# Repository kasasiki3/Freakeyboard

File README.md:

# Freakeyboard
You enter keys into your PC by swiping and touching just like on a smartphone keyboard.

This keyboarad has 23tuch senser and Raspberry Pi pico .

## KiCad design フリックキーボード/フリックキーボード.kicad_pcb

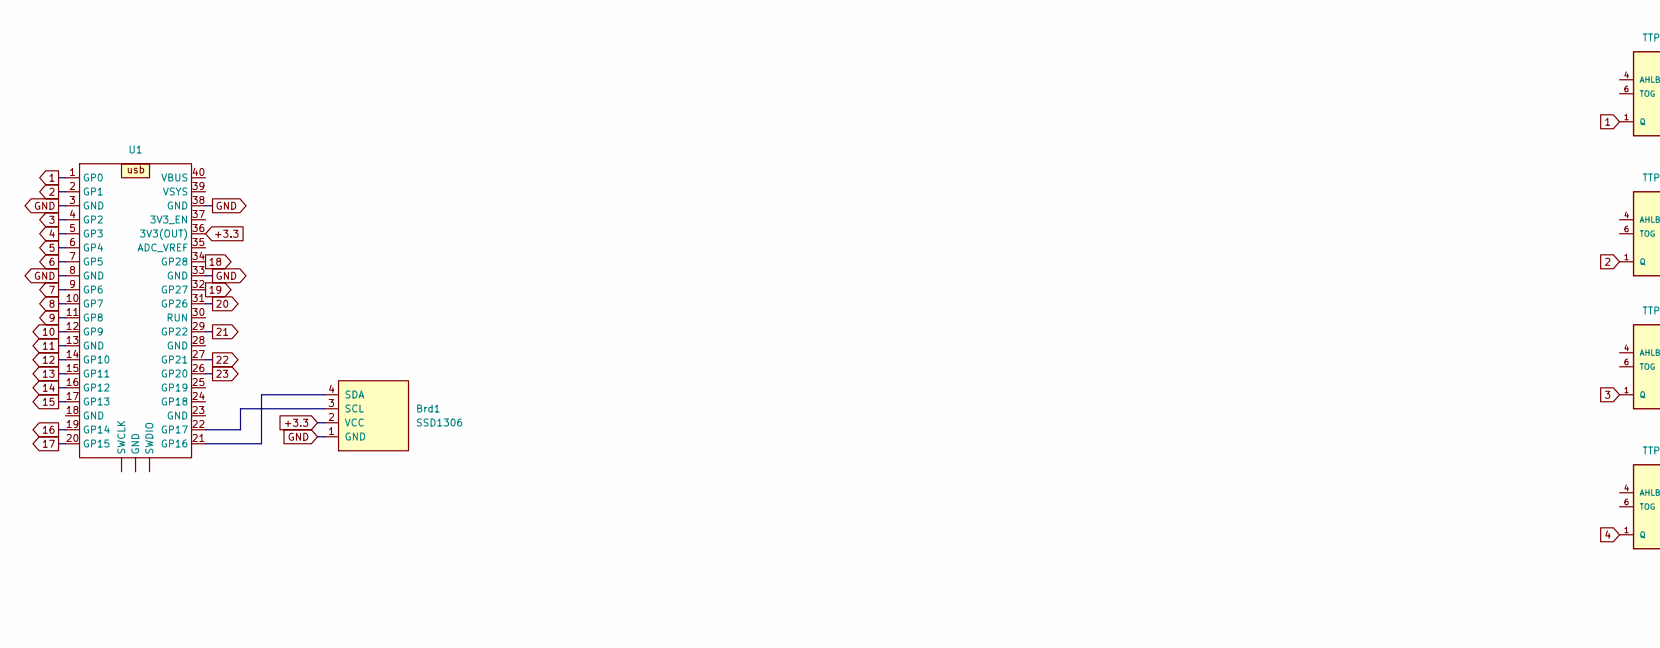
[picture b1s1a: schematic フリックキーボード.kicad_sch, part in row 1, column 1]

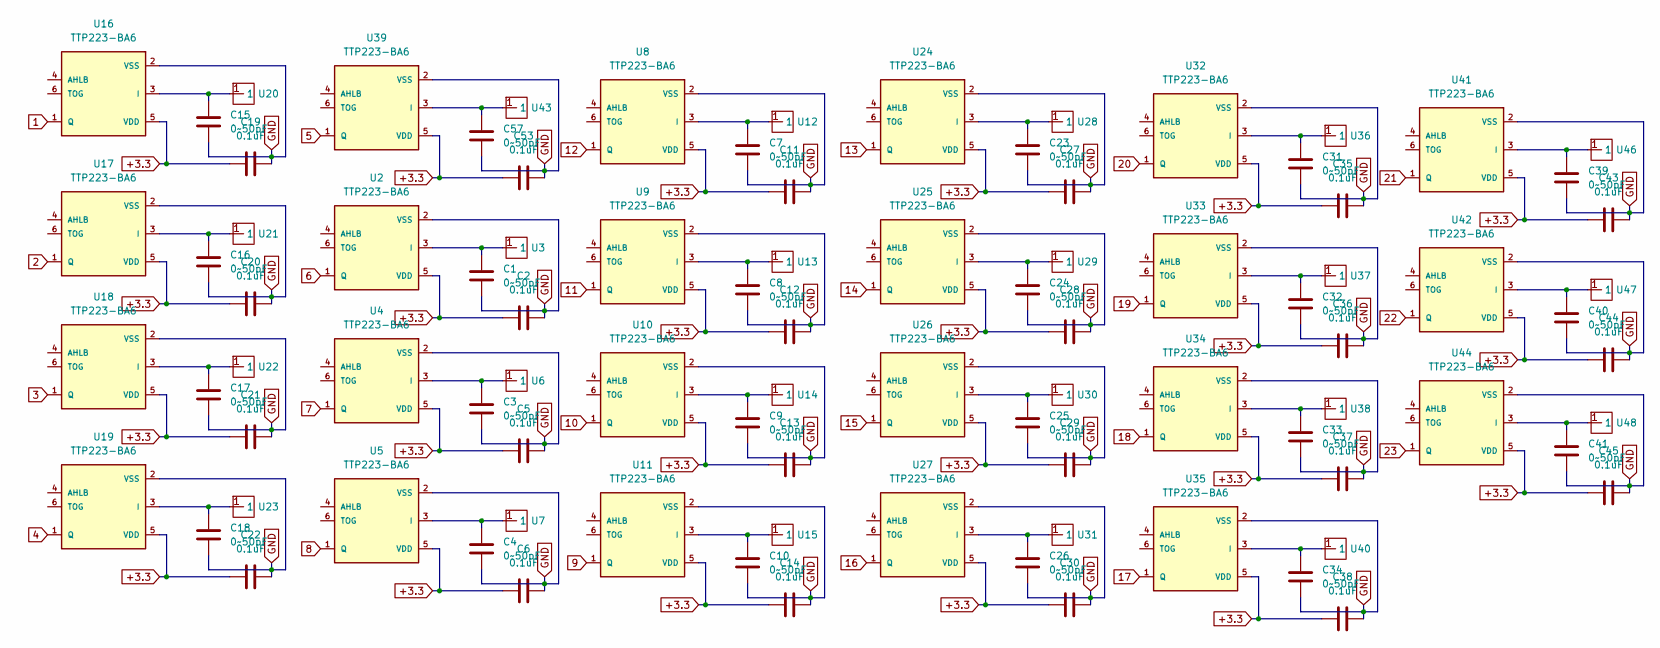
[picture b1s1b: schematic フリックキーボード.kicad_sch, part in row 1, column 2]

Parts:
Brd1: SSD1306; 128x64OLED
C1, C3, C4, C7, C8, C9, C10, C15, C16, C17, C18, C23, C24, C25, C26, C31, C32, C33, C34, C39, C40, C41, C57: 0~50pF; C_0603_1608Metric
C2, C5, C6, C11, C12, C13, C14, C19, C20, C21, C22, C27, C28, C29, C30, C35, C36, C37, C38, C43, C44, C45, C53: 0.1uF; C_0603_1608Metric
U1: RPi_Pico_SMD_TH
U2, U4, U5, U8, U9, U10, U11, U16, U17, U18, U19, U24, U25, U26, U27, U32, U33, U34, U35, U39, U41, U42, U44: TTP223-BA6; SOT23-6
U3, U6, U7, U12, U13, U14, U15, U20, U21, U22, U23, U28, U29, U30, U31, U36, U37, U38, U40, U43, U46, U47, U48: 13×13 touch pad

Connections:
1: U1.1 (GP0), U16.1 (Q)
2: U1.2 (GP1), U17.1 (Q)
3: U1.4 (GP2), U18.1 (Q)
4: U1.5 (GP3), U19.1 (Q)
5: U1.6 (GP4), U39.1 (Q)
6: U1.7 (GP5), U2.1 (Q)
7: U1.9 (GP6), U4.1 (Q)
8: U1.10 (GP7), U5.1 (Q)
9: U1.11 (GP8), U11.1 (Q)
10: U1.12 (GP9), U10.1 (Q)
11: U1.13 (GND), U9.1 (Q)
12: U1.14 (GP10), U8.1 (Q)
13: U1.15 (GP11), U24.1 (Q)
14: U1.16 (GP12), U25.1 (Q)
15: U1.17 (GP13), U26.1 (Q)
16: U1.19 (GP14), U27.1 (Q)
17: U1.20 (GP15), U35.1 (Q)
18: U1.34 (GP28), U34.1 (Q)
19: U1.32 (GP27), U33.1 (Q)
20: U1.31 (GP26), U32.1 (Q)
21: U1.29 (GP22), U41.1 (Q)
22: U1.27 (GP21), U42.1 (Q)
23: U1.26 (GP20), U44.1 (Q)
+3.3: Brd1.2 (VCC), C2.2, C5.2, C6.2, C11.2, C12.2, C13.2, C14.2, C19.2, C20.2, C21.2, C22.2, C27.2, C28.2, C29.2, C30.2, C35.2, C36.2, C37.2, C38.2, C43.2, C44.2, C45.2, C53.2, U1.36 (3V3(OUT)), U2.5 (VDD), U4.5 (VDD), U5.5 (VDD), U8.5 (VDD), U9.5 (VDD), U10.5 (VDD), U11.5 (VDD), U16.5 (VDD), U17.5 (VDD), U18.5 (VDD), U19.5 (VDD), U24.5 (VDD), U25.5 (VDD), U26.5 (VDD), U27.5 (VDD), U32.5 (VDD), U33.5 (VDD), U34.5 (VDD), U35.5 (VDD), U39.5 (VDD), U41.5 (VDD), U42.5 (VDD), U44.5 (VDD)
GND: Brd1.1 (GND), C1.2, C2.1, C3.2, C4.2, C5.1, C6.1, C7.2, C8.2, C9.2, C10.2, C11.1, C12.1, C13.1, C14.1, C15.2, C16.2, C17.2, C18.2, C19.1, C20.1, C21.1, C22.1, C23.2, C24.2, C25.2, C26.2, C27.1, C28.1, C29.1, C30.1, C31.2, C32.2, C33.2, C34.2, C35.1, C36.1, C37.1, C38.1, C39.2, C40.2, C41.2, C43.1, C44.1, C45.1, C53.1, C57.2, U1.3 (GND), U1.8 (GND), U1.33 (GND), U1.38 (GND), U2.2 (VSS), U4.2 (VSS), U5.2 (VSS), U8.2 (VSS), U9.2 (VSS), U10.2 (VSS), U11.2 (VSS), U16.2 (VSS), U17.2 (VSS), U18.2 (VSS), U19.2 (VSS), U24.2 (VSS), U25.2 (VSS), U26.2 (VSS), U27.2 (VSS), U32.2 (VSS), U33.2 (VSS), U34.2 (VSS), U35.2 (VSS), U39.2 (VSS), U41.2 (VSS), U42.2 (VSS), U44.2 (VSS)
unnamed: Brd1.3 (SCL), U1.22 (GP17)
unnamed: Brd1.4 (SDA), U1.21 (GP16)
unnamed: C1.1, U2.3 (I), U3.1
unnamed: C3.1, U4.3 (I), U6.1
unnamed: C4.1, U5.3 (I), U7.1
unnamed: C7.1, U8.3 (I), U12.1
unnamed: C8.1, U9.3 (I), U13.1
unnamed: C9.1, U10.3 (I), U14.1
unnamed: C10.1, U11.3 (I), U15.1
unnamed: C15.1, U16.3 (I), U20.1
unnamed: C16.1, U17.3 (I), U21.1
unnamed: C17.1, U18.3 (I), U22.1
unnamed: C18.1, U19.3 (I), U23.1
unnamed: C23.1, U24.3 (I), U28.1
unnamed: C24.1, U25.3 (I), U29.1
unnamed: C25.1, U26.3 (I), U30.1
unnamed: C26.1, U27.3 (I), U31.1
unnamed: C31.1, U32.3 (I), U36.1
unnamed: C32.1, U33.3 (I), U37.1
unnamed: C33.1, U34.3 (I), U38.1
unnamed: C34.1, U35.3 (I), U40.1
unnamed: C57.1, U39.3 (I), U43.1
unnamed: C39.1, U41.3 (I), U46.1
unnamed: C40.1, U42.3 (I), U47.1
unnamed: C41.1, U44.3 (I), U48.1

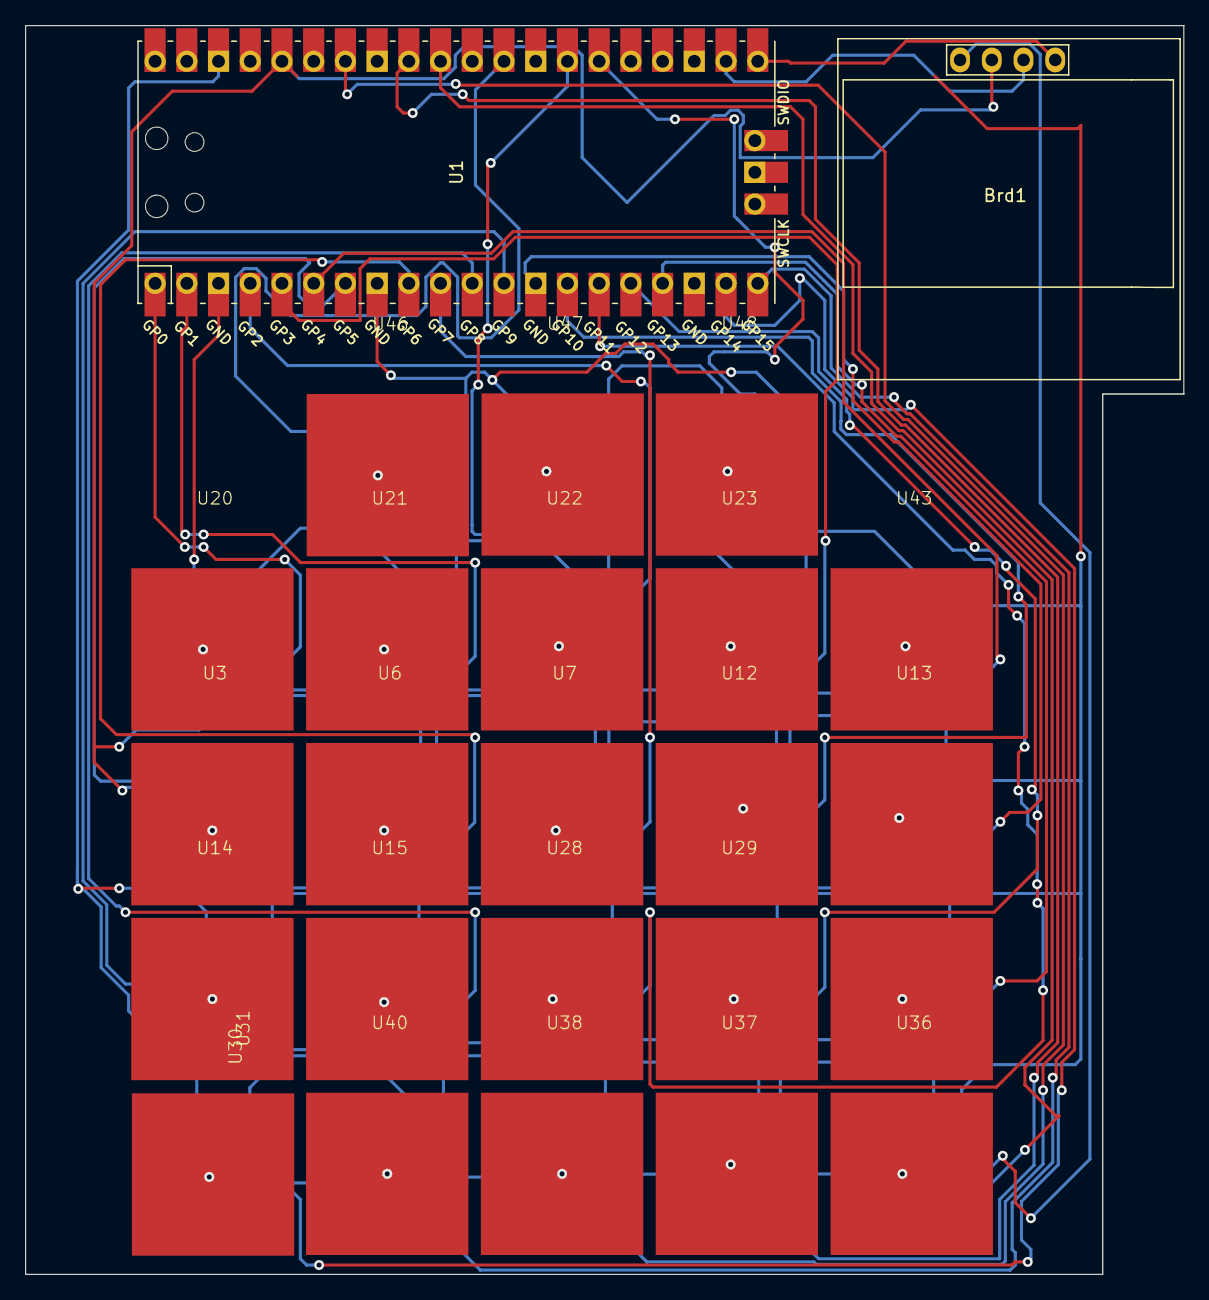
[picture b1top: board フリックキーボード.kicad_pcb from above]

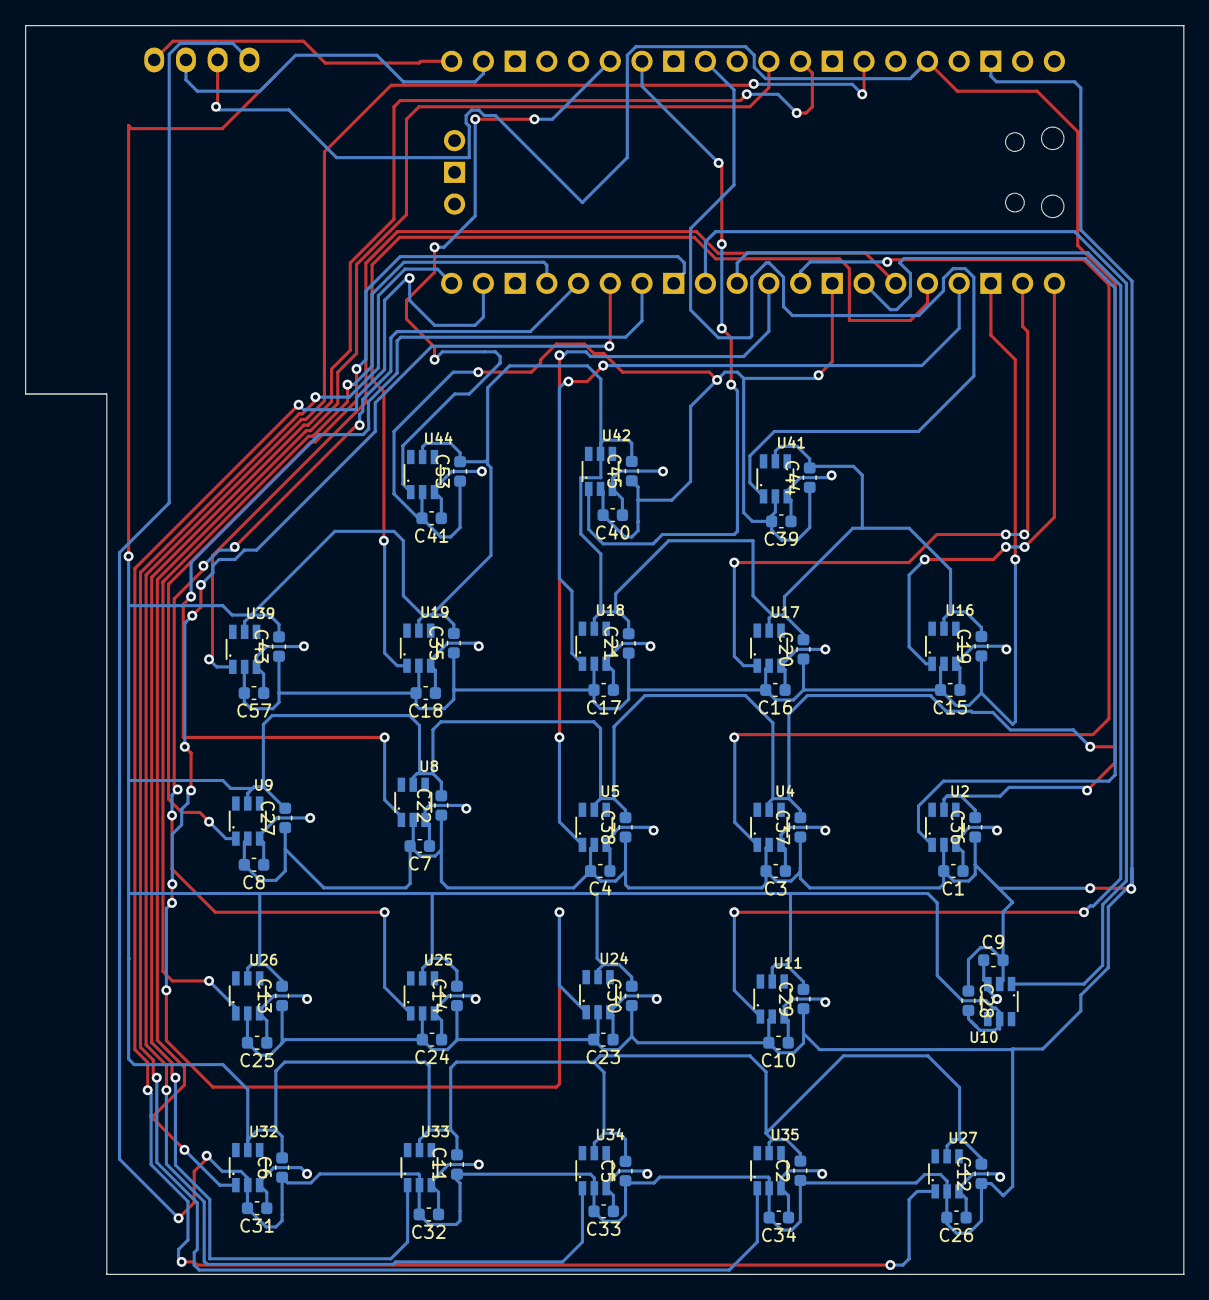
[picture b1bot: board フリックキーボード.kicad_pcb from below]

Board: 2 copper layers, 92.8 x 100.0 mm, 94 parts (69 on the bottom side), 50 nets.
